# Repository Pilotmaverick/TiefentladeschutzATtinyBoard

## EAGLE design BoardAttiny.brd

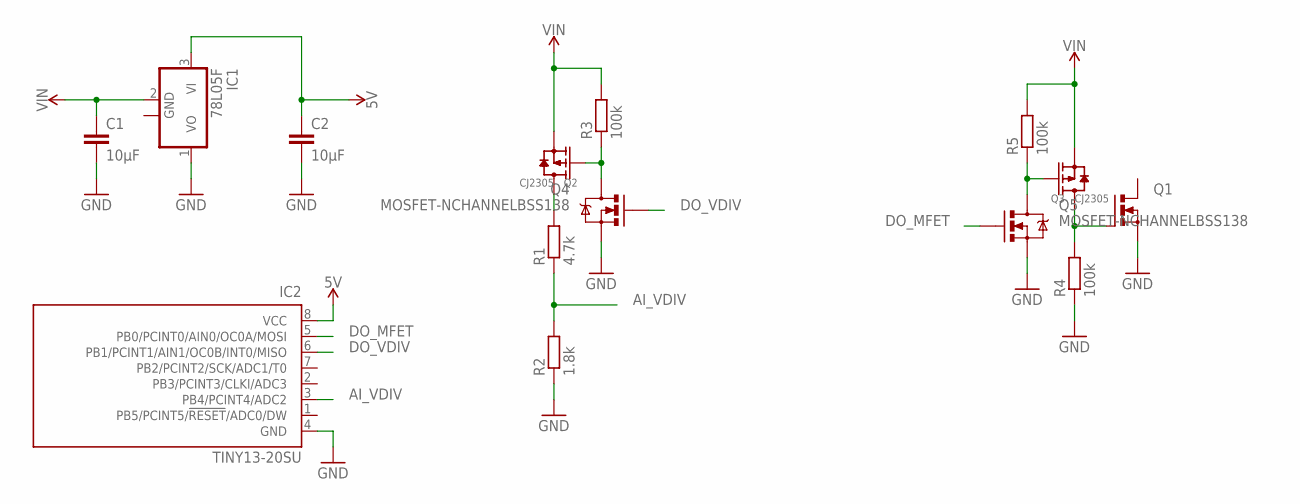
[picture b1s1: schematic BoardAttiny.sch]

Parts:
C1, C2: 10µF; C0805
IC1: 78L05F; SOT89
IC2: TINY13-20SU; 8S2
Q1: PMOSFET_NTO220BH; TO220BH
Q2, Q3: CJ2305; SOT-23
Q4, Q5: MOSFET-NCHANNELBSS138; SOT23
R1: 4.7k; R0805
R2: 1.8k; R0805
R3, R4, R5: 100k; R0805

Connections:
5V: C2.1, IC1.3 (VI), IC2.8 (VCC)
AI_VDIV: IC2.3 (PB4/PCINT4/ADC2), R1.1, R2.2
DO_MFET: IC2.5 (PB0/PCINT0/AIN0/OC0A/MOSI), Q5.1 (G)
DO_VDIV: IC2.6 (PB1/PCINT1/AIN1/OC0B/INT0/MISO), Q4.1 (G)
GND: C1.2, C2.2, IC1.1 (VO), IC2.4 (GND), Q1.S, Q4.2 (S), Q5.2 (S), R2.1, R4.1
unnamed: Q2.3 (D), R1.2
unnamed: Q2.1 (G), Q4.3 (D), R3.1
unnamed: Q3.1 (G), Q5.3 (D), R5.1
unnamed: Q1.G, Q3.3 (D), R4.2
VIN: C1.1, IC1.2 (GND), Q2.2 (S), Q3.2 (S), R3.2, R5.2

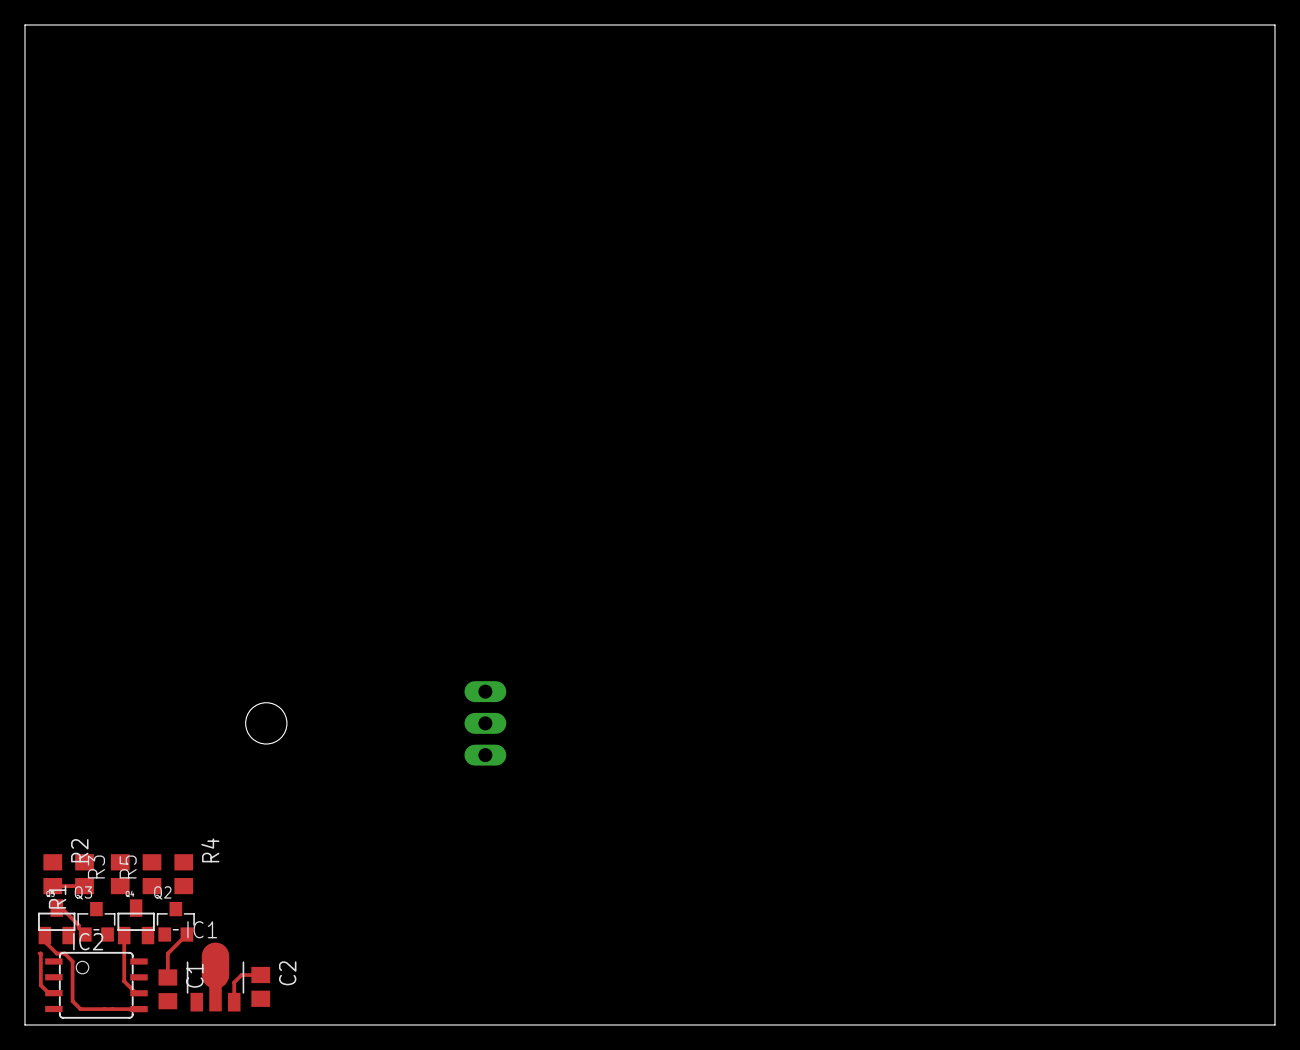
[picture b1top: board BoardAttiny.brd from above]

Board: 2 copper layers, 100.0 x 80.0 mm, 14 parts (1 on the bottom side), 10 nets.

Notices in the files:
parts and their libraries:
SparkFun-PowerSymbols: Licensing: Creative Commons ShareAlike 4.0 International - https://creativecommons.org/licenses/by-sa/4.0
